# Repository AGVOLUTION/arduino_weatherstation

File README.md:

## Wie viel hat es kürzlich auf meinem Feld tatsächlich geregnet?
_What was the last on-site rain amount on my farm?_
## Ist die Temperatur im Pflanzenbestand die selbe, wie die der nächsten Wetterstation?
_Does the temperature of the public weatherstation and inside the plants match?_

## Wir helfen dir, kostengünstig und simpel eine eigene Wetterstation in Betrieb zu nehmen.
Wir stellen dir die Anbindung ans Internet, Datenauswertung und -visualisierung kostenlos und unkompliziert zur Verfügung.

We help you to install your own low-cost weatherstation. Connectivity and data storage, evaluation and -visualization is provided by us.

# Agvolution Open-Source Weatherstation
Embedded software and hardware design for Arduino MKR-board based Weatherstation (Atmel SAMD processors).

## Frequently Asked Questions (FAQ)
1. How can I build my own Weatherstation? _We have published a KiCad schematic, PCB-layout, Bill of Materials, and the embedded firmware - including pre-built binaries. You can either buy a complete Weatherstation or a DIY-kit (assembled PCB) from Agvolution GmbH or start from scratch by ordering and assembling all the components (PCB, electronic components, sensors, housing, etc.) on your own. Do not hesitate to contact us! (contact@agvolution.com)_
2. How can I customize the configuration (e.g. packet transmit, wind sampling, position periods, etc.)? _You can make adjustments to the transmit and sampling periods in Inc/commission/commission.h and then rebuild the project. We also provide pre-built binaries with different configurations (check the builds folder)._
3. Which sensors can I connect? _Please check the list below (supported sensors). You can simply integrated new sensors by adjusting the firmware. Let us know about your changes, we can then merge your pull-request (reach out to l.kamm@agvolution.com)._
4. What is the battery life time of my station? _We have provided an energy-benchmark table in the energy-benchmark folder. On the one hand, it contains energy measurements on the real system. On the other hand, it contains a parametric energy consumption simulation. You can use it to estimate the battery life time depending on your system configuration._
5. Can I connect a solar module? _Yes, you can. We will provide further information soon._
6. Which LPWANs are available? _The first version was built on SigFox. We can easily integrate other boards (Nb-IoT, LoRa, Bluetooth, WiFi, ...). Feel free to contact us._
7. How can I access the data? _There exist two methods: 1) You can register your Arduino MKRFox1200 board in the SigFox backend using the ID and PAC programmed to the RF chip. You have then access to the raw payloads. 2) You can register your Arduino MKRFox1200 board with Agvolution or buy a pre-programmed and pre-registered board at us. You have then access to the climate data (human-readable) via a Smartphone App (iOS, Android) [Farmalyzer], IoT-platform in the browser (charts, position, etc.) [https://iot.agvolution.com] and via a data API (GraphQL). Data storage, payload decoding, visualization - we do it for you! You can manage users and share your data with your partners on our platform. You can also make use of our application software services (recommendations, models, etc.). Reach out to us (contact@agvolution.com)._

## Supported sensors
At the moment, we support:
* Sensirion SHT3x (I2C-addresses 0x44 and 0x45)
* Bosch BME280 (I2C-addresses 0x76 and 0x77)
* DS18B20 (arbitrary address, automatic address scan, selecting the first available sensor on the 1-wire bus)
* Watermark soil matrix potential (up to 4x)
* GNSS satellite positioning module
* Rain Gauge (up to 2 passive, tipping spoon reed contact sensors)
* Wind direction (analog poti) and speed (passive contact pulse)
* Weight Cell (we have included a temperature-stable, low-noise instrumentation amplifier. It can be used to read weight cells (German: Dehnungsmessstreifen, DMS). Used for bee hive weight monitoring, ...)

## Custom configuration
* Edit Inc/commission/commission.h and build the project.
* Alternatively, you can use the pre-built binaries in the builds-folder

## Build the project
**Required Arduino libraries:**
* Arduino Low Power (by Arduino LLC), v1.2.2
* Arduino SigFox for MKRFox1200 (by Arduino LLC), v1.0.4
* RTCZero (by Arduino), v1.6.0
* SD (by Arduino), v1.2.4
* BlueDot BME280 Library (by BlueDot), v1.0.9
* DS18B20 (by Mathias Munk Hansen), v1.0.0
* FlashStorage (by Arduino), v1.0.0
* OneWire (by Paul Stoffregen), v2.3.5
* SHT31 (by Rob Tillaart), v.0.3.4

**Required Arduino boards:**
* Arduino SAMD Boards (32-bits ARM Cortex M0+) (by Arduino), v1.8.11

**Instructions**
1. Clone the project
2. Open arduino_weatherstation.ino in Arduino IDE. Install the required library and board packages.
3. Build + Flash.
4. Done!

## Hardware Installation
### Solar Panel
1. Cut the DC jack.

2. Strip the two wires and twist the ends.

3. Install the JST connector at the respective clamp. Please take care of the polarity ( + red, - black ). Also, replace the screw next to the GPS module area by a hex distance bolt. You can use Loctite to fix the screws.

4. Conduct the solar wire through one of the housing cable mounts. Bend the copper wires 180°, insert them on the Solar Charger Module at PWR IN (+ red, - blue) and tighten the screws. To improve the durability, make sure, that the screws of the clamp not only fasten the thin copper wires, but also the plastic moulding of the cables. Mount the Solar Charger Module on the hex nut and connect the JST cable to the socket. The status LEDs should be on, when the module is placed in the sun.

### Anemometer (Davis)
1. Cut off the RJ11 connector.

2. Use the 4-pin clamp in the PCB corner, labelled with 'Davis Anemometer'.

3. Strip the wire and drill the ends. Insert the wires into the clamp while pressing down the bolt, using a screwdriver or a similar tool. Please take care of the wire colors (Y: yellow, G: green, R: red, B: black).

## ToDo
* If BME76 and BME77 looses initialization (power cut) -> Detect and Re-Init ? Which registers need to be written?
* Integration of LoRa, mioty, Nb-IoT boards

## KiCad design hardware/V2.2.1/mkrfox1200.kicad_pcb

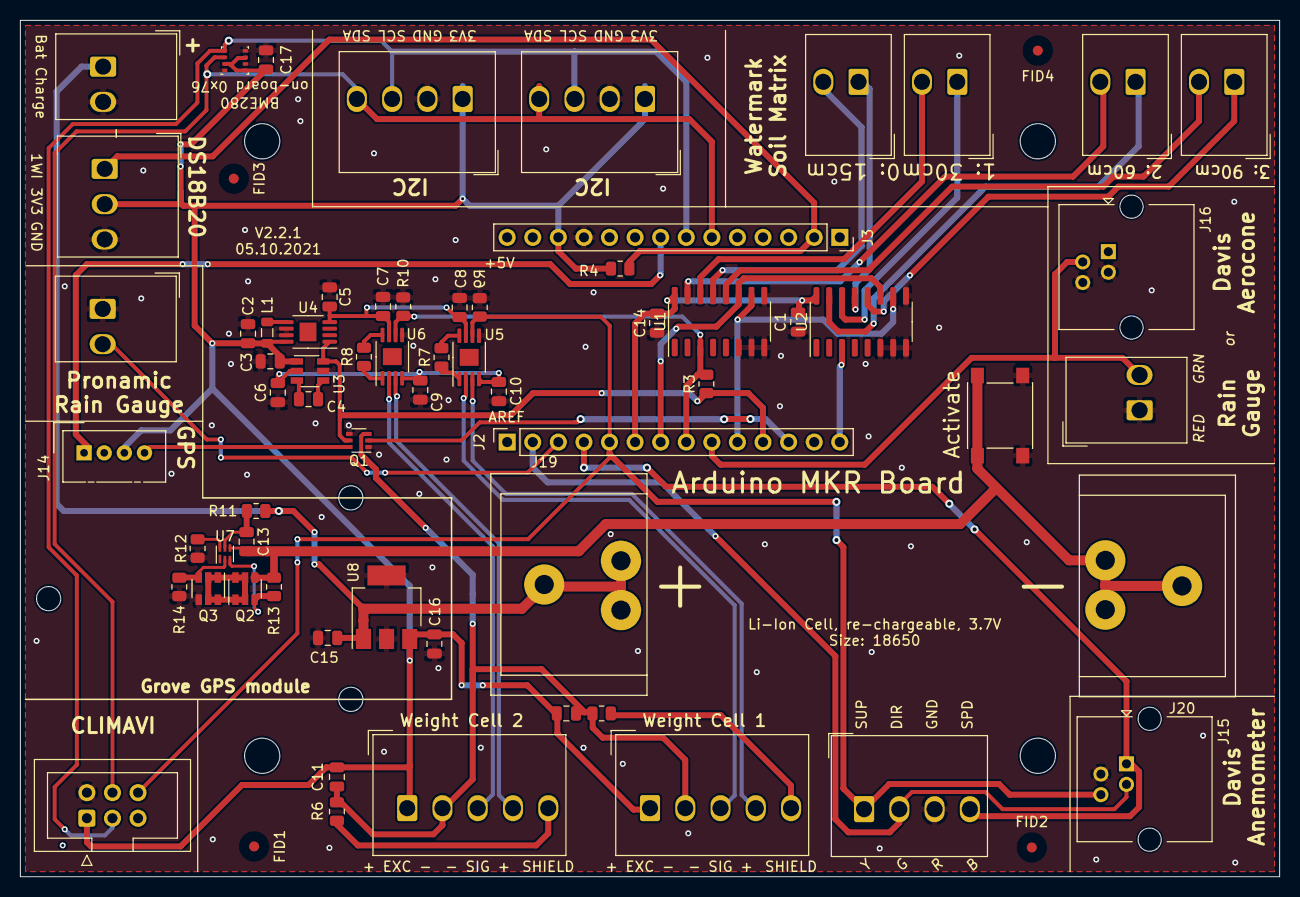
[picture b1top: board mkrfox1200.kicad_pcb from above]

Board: 2 copper layers, 125.0 x 85.0 mm, 69 parts (1 on the bottom side), 50 nets.

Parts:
C1, C2, C3, C4, C5, C6, C7, C8, C9, C10, C11, C12, C13, C14, C17: 100nF; C_0805_2012Metric
C15, C16: 4.7uF; C_0805_2012Metric
FID1, FID2, FID3, FID4: Fiducial; Fiducial_1mm_Mask3mm
J1, J5, J6, J8, J9, J10: Conn_01x02_Male; Phoenix_19_84_96_3_1x02_P3.50mm_Vertical
J2, J3: Conn_01x14_Female; PinSocket_1x14_P2.54mm_Vertical
J4, J12, J13: Conn_01x04_Male; Phoenix_19_84_98_9_1x04_P3.50mm_Vertical
J7: Conn_02x03_Odd_Even; IDC-Header_2x03_P2.54mm_Vertical
J11: Conn_01x03_Male; Phoenix_19_84_97_6_1x03_P3.50mm_Vertical
J14: Conn_01x04_Male; NS-Tech_Grove_1x04_P2mm_Vertical
J15, J16: RJ14; RJ14_Wuerth_615004138421_Horizontal
J17, J18: Conn_01x05_Female; Phoenix_19_84_99_2_1x05_P3.50mm_Vertical
J19, J20: Conn_01x01_Female; BatteryClip_Keystone_54
J21: Conn_01x02; Phoenix_19_84_96_3_1x02_P3.50mm_Vertical
L1: 4.7uH; L_0805_2012Metric
Q1: DMN65D8LDW; SOT-363_SC-70-6
Q2, Q3: DMN3115UDM; SOT-23-6
QR*****: QR_Code_agvolution.com
R3: 7.87k; R_0805_2012Metric
R4: 10k; R_0805_2012Metric
R5, R6: 0; R_0805_2012Metric
R7, R8: 150; R_0805_2012Metric
R9, R10: 33k; R_0805_2012Metric
R11: 330; R_0805_2012Metric
R12: 2k2; R_0805_2012Metric
R13, R14: 4.7M; R_0805_2012Metric
SW1: SW_Push; SW_SPST_PTS645
U1, U2: 4051; SO-16_3.9x9.9mm_P1.27mm
U3: LTC1983-5; TSOT-23-6
U4: MCP1642B-50; MSOP-8-1EP_3x3mm_P0.65mm_EP1.68x1.88mm
U5, U6: INA126; MSOP-8-1EP_3x3mm_P0.65mm_EP1.68x1.88mm
U7: BQ297xy; WSON-6_1.5x1.5mm_P0.5mm
U8: ZLDO1117G33TA; SOT-223-3_TabPin2
U9: BME280; Bosch_LGA-8_2.5x2.5mm_P0.65mm_ClockwisePinNumbering

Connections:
+3V3: C2.2, C3.2, C11.1, C12.1, C16.2, C17.1, J3.12, J7.1, J11.2, J12.1, J13.1, J14.3, J17.1, J18.1, L1.1, R4.2, U3.1, U4.8, U8.3, U9.2, U9.6, U9.8
+5V: C5.1, C7.1, C8.1, U4.4, U5.7, U6.7
-5V: C6.1, C9.1, C10.1, U3.2, U5.4, U6.4
AGV_MOISTURE_EN: J2.5, J4.1, J7.6, J15.4, R9.1, U5.6
DAVIS_RAIN: J2.9, J5.2, J16.2
DAVIS_WIND_DIR: J2.2, J4.2, J15.3
DAVIS_WIND_SPD: J2.4, J4.4, J15.1
DS18B20_1W: J3.2, J11.1, R4.1
EXC-_1: C11.2, C12.2, J17.2, J18.2, Q1.3, R5.1, R6.1
GND: C1.2, C2.1, C3.1, C5.2, C6.2, C7.2, C8.2, C9.2, C10.2, C14.2, C15.1, C16.1, C17.2, J1.1, J3.11, J4.3, J5.1, J7.2, J11.3, J12.2, J13.2, J15.2, J16.3, J16.4, J21.2, Q1.1, Q1.4, Q3.4, R9.2, R10.2, R12.1, R14.1, SW1.1, U1.6, U1.7, U1.8, U1.9, U2.6, U2.7, U2.8, U2.9, U3.5, U4.6, U4.7, U5.5, U6.5, U8.2, U9.1, U9.5, U9.7
GPS_SUP: J2.12, Q1.2
GPS_TX: J3.8, J14.1
unnamed: C4.1, U3.4
unnamed: C4.2, U3.3
unnamed: C13.1, R11.2, U7.5
unnamed: C13.2, J20.1, Q2.4, R13.1, SW1.2, U7.4
unnamed: J6.1, U2.13
unnamed: J6.2, U1.13
unnamed: J8.1, U2.14
unnamed: J8.2, U1.14
unnamed: J9.1, U2.15
unnamed: J9.2, U1.15
unnamed: J10.1, U2.12
unnamed: J10.2, U1.12
unnamed: J14.4, Q1.6
unnamed: L1.2, U4.5
unnamed: Q2.1, Q2.2, Q2.5, Q2.6, Q3.1, Q3.2, Q3.5, Q3.6
unnamed: Q2.3, R13.2, U7.3
unnamed: Q3.3, R14.2, U7.2
unnamed: R7.1, U5.1
unnamed: R7.2, U5.8
unnamed: R8.1, U6.1
unnamed: R8.2, U6.8
unnamed: R12.2, U7.6
PRONAMIC_RAIN: J1.2, J2.3
SCL: J3.7, J7.3, J12.3, J13.3, U9.4
SDA: J3.6, J7.4, J12.4, J13.4, U9.3
SHLD1: J17.5, R5.2
SHLD2: J18.5, R6.2
SIG+_1: J17.3, U5.2
SIG+_2: J18.3, U6.2
SIG-_1: J17.4, U5.3
SIG-_2: J18.4, U6.3
VBAT+: C15.2, J19.1, J21.1, R11.1, U8.1
WEIGHT_2: J2.8, R3.1, R10.1, U1.3, U6.6
WEIGHT_EN: J2.11, Q1.5, R3.2, U3.6, U4.1
WM_A: J2.7, U1.11, U2.11
WM_B: J2.10, U1.10, U2.10
WM_EXC2: J2.14, U2.3
WM_SWITCH_SUP: C1.1, C14.1, J2.6, U1.16, U2.16

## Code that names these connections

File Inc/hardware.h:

/*
MIT License

Copyright (c) 2021 Agvolution
Head Development: Lukas Kamm / l.kamm@agvolution.com

Permission is hereby granted, free of charge, to any person obtaining a copy
of this software and associated documentation files (the "Software"), to deal
in the Software without restriction, including without limitation the rights
to use, copy, modify, merge, publish, distribute, sublicense, and/or sell
copies of the Software, and to permit persons to whom the Software is
furnished to do so, subject to the following conditions:

The above copyright notice and this permission notice shall be included in all
copies or substantial portions of the Software.

THE SOFTWARE IS PROVIDED "AS IS", WITHOUT WARRANTY OF ANY KIND, EXPRESS OR
IMPLIED, INCLUDING BUT NOT LIMITED TO THE WARRANTIES OF MERCHANTABILITY,
FITNESS FOR A PARTICULAR PURPOSE AND NONINFRINGEMENT. IN NO EVENT SHALL THE
AUTHORS OR COPYRIGHT HOLDERS BE LIABLE FOR ANY CLAIM, DAMAGES OR OTHER
LIABILITY, WHETHER IN AN ACTION OF CONTRACT, TORT OR OTHERWISE, ARISING FROM,
OUT OF OR IN CONNECTION WITH THE SOFTWARE OR THE USE OR OTHER DEALINGS IN THE
SOFTWARE.
*/

#ifndef _HARDWARE_H
#define _HARDWARE_H

/* Specify hardware layout */
#define DS18B20_Pin             7

#define WM_EXC2_Pin             5
#define SDLOG_CS_Pin            4
#define GPS_SUP_Pin             3
#define WM_EXC1_Pin             2
#define WEIGHT_EN_Pin			2
#define WM_B_Pin                1
#define RAIN_DAVIS_Pin     		0
#define WM_RESISTANCE_Pin       (PIN_A6)
#define WEIGHT_2_Pin			(PIN_A6)
#define WM_A_Pin                (PIN_A5)
#define WM_SWITCH_SUP           (PIN_A4)
#define AGV_MOISTURE_EN_Pin     (PIN_A3)
#define WIND_SUP_Pin      		(PIN_A3)
#define WEIGHT_1_Pin			(PIN_A3)
#define WIND_SPD_Pin      		(PIN_A2)
#define RAIN_PRONAMIC_Pin  		(PIN_A1)
#define WIND_DIR_Pin      		(PIN_A0)

#endif // _HARDWARE_H

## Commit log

2021-05-20 Having the rain count timestamp reset after TX corrected.
2021-05-20 Feature: Persistently store accumulated rain in flash storage.
2021-05-20 Count rain events also during wind sampling
2021-05-20 Adding logfiles to test the davis rain count
2021-07-18 Prototyping with the GPS module
2021-07-18 Read Watermark Soil Matrix Potential sensors.
2021-07-18 GPS module prototyping via multiple serial ports.
2021-07-18 Generate a rectangular signal on a separate Arduino board in order to test the functionality of the tipping spoon interrupt.
2021-07-18 Reorganizing files
2021-07-18 Major update of module libraries: 1. Reorganizing the BME280 interface, 2. Modernizing the wind and rain module 3. Adding a simple debug module 4. Adding a equipment list module 5. Adding a custom RT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
2021-07-18 Major software update: Coping with the new v2.0.0 pcb -> Able to read multiple external sensors: 2x BME280, Multiple DS18B20 (automatic address detection), 4x Watermark Soil Matrix Potential, Davis A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
2021-09-16 Bugfix: Rain counter (current) was not reset since method body was not implemented.
2021-09-16 Watermark: Preventing a leakage current through switch select pins A + B
2021-09-16 Serial Debug Output. Modifications to GPS fixture times.
2021-09-16 Removing Debug Serial and Debug No LPMODE flag.
2021-10-20 Changing GPS packet frequency to every three days instead of every two days. UART debug frequency is 38400
2021-10-24 Implementing SD LOG module.
2021-10-24 Bugfix: Names of Parameters and Attributes were identical. Led to wrong pin numbers in wind module.
2021-10-24 Adding SHT30 to equipment list and removing leaf wetness.
2021-10-24 Using placeholder macro for debug serial device
2021-10-24 Using new payload formats 105,106,107
2021-10-24 Updating hardware layout and timing parameters for new Version 2.2.2
2021-10-24 New payload format integration. Dual rain sensor. Dual SHT3x T/RH sensor.
2021-11-13 Adding Weatherstation Energy Benchmark files
2021-12-10 Adding position information extraction code for SIM28 module besides old u.blox module.
2021-12-10 Adding latest build
2021-12-10 Adding C++ gitignore
2022-03-02 Commenting weight.cpp
2022-03-02 Adding new build
2022-03-02 adding first conf build!
2022-04-08 Cleanup on master branch. Developing files are still available on branch prototyping
2022-04-08 Removing device lists
2022-04-08 Removing notes. Still available on branch prototyping.
2022-04-08 Minor code beautifying.
2022-05-14 Variance-estimator is normalized to 1/(n-1) instead of 1/n.
2022-05-15 Adding hardware layout v2.2.1
2022-05-15 Moving Arduino Board schematics
2022-05-15 Removing unused commission files.
2022-05-15 Updating energy-benchmark table -> Better overview, english
2022-05-15 Renaming main
2022-05-15 Correcting licensing and add build info segment
2022-05-15 Adding more pre-built binaries and instructions.
2022-05-15 Fixing license
2022-06-20 Adding installation images
2022-06-20 Add installation instructions.
2022-07-22 DFKI only wind 5 minutes feature
